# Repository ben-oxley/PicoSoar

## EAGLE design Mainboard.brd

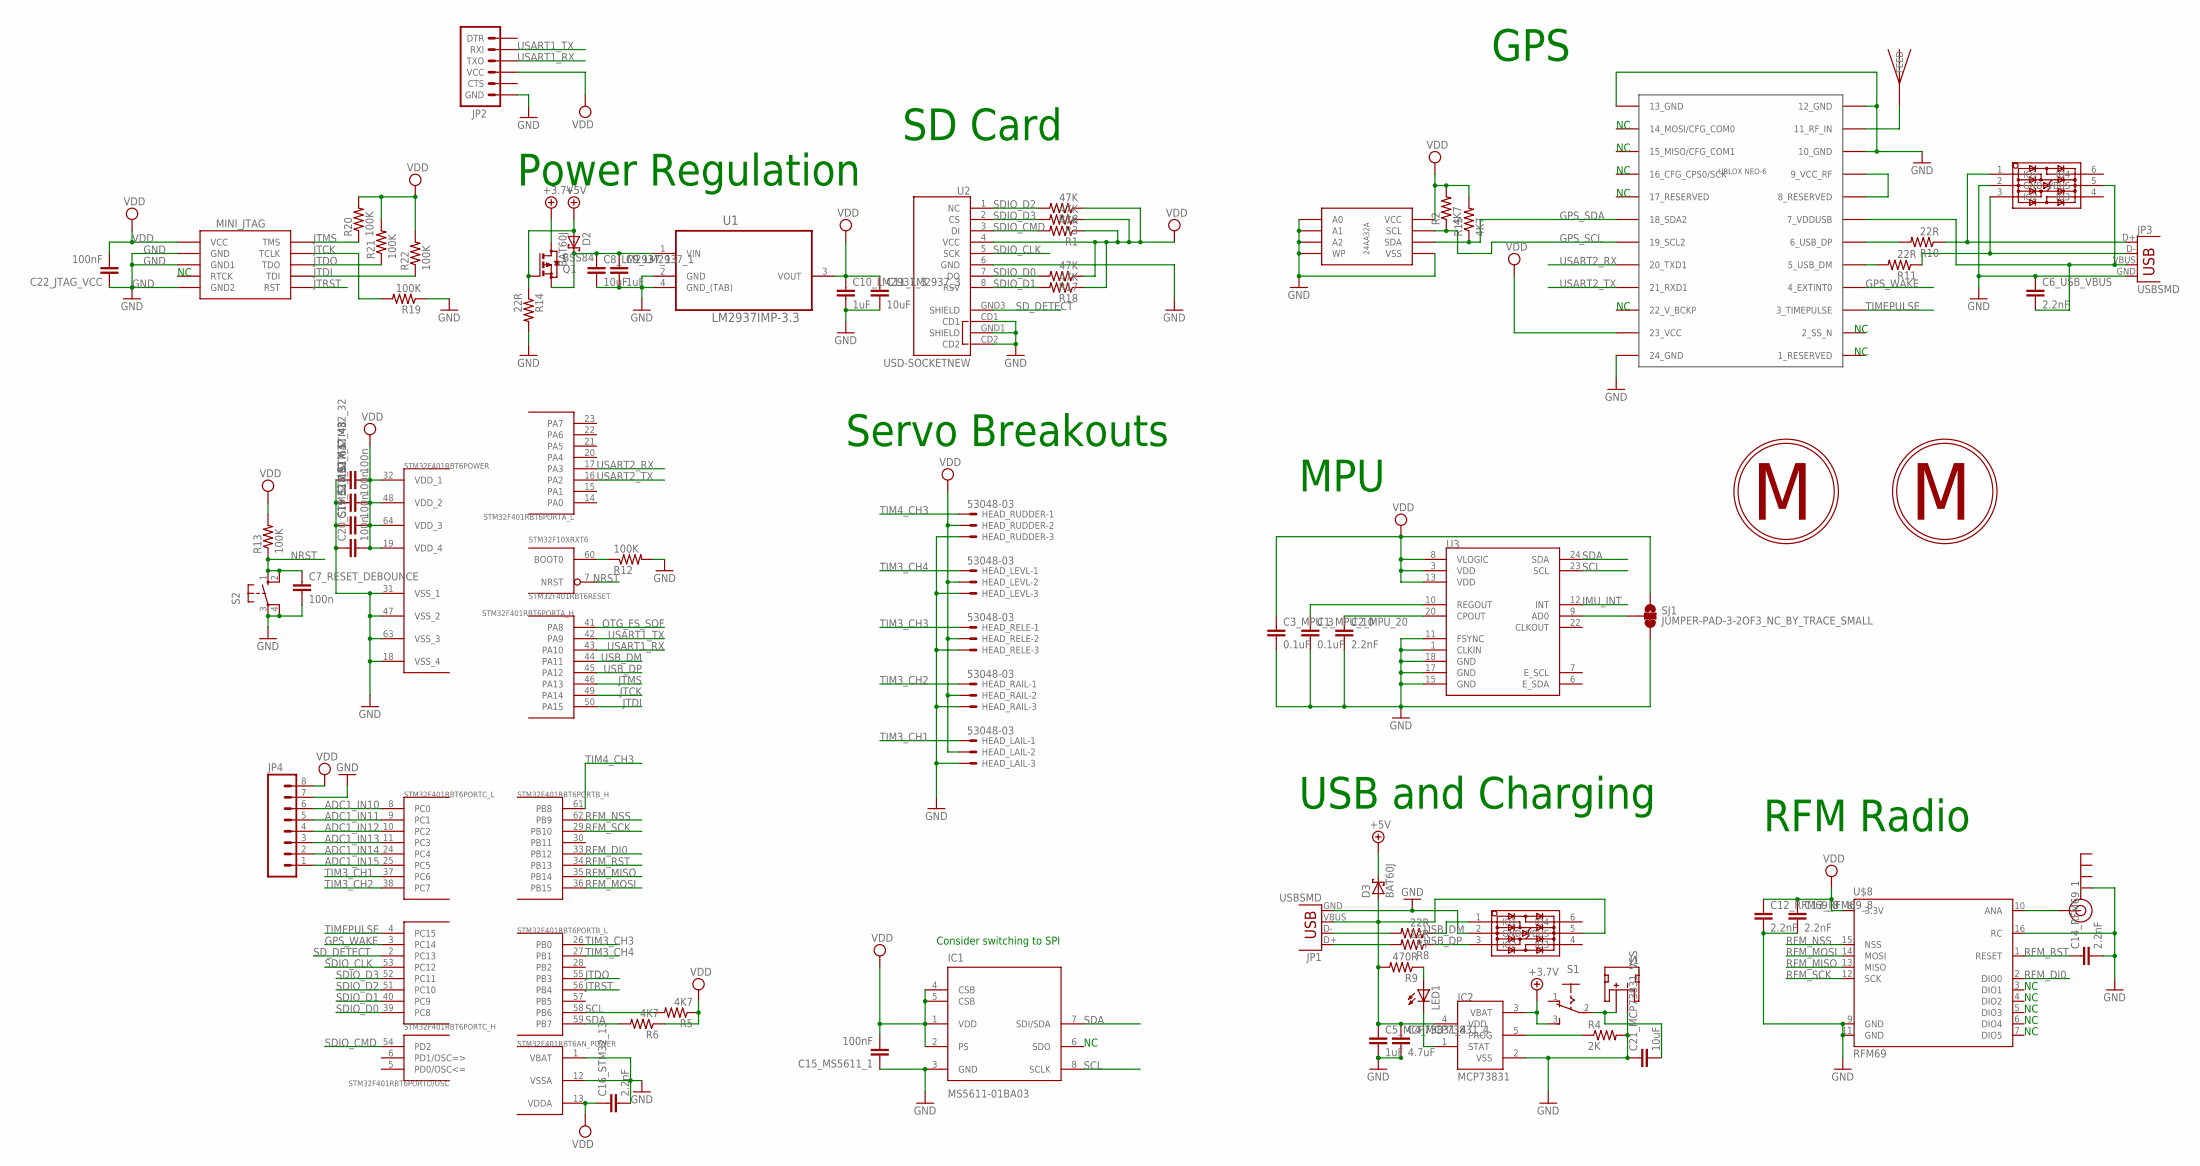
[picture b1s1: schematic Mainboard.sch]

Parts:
C1_MPU_10, C3_MPU_3: 0.1uF; 0805
C2_MPU_20, C6_USB_VBUS, C12_RFM69_8, C13_RFM69_8, C14_RFM69_1, C16_STM32_13: 2.2nF; 0805
C4_MCP73831_4: 4.7uF; 0805
C5_MCP73831_4, C9_LM2937_1, C10_LM2937_3: 1uF; 0805
C7_RESET_DEBOUNCE, C17_STM32_32, C18_STM32_48, C19_STM32_64, C20_STM32_19: 100n; 0805
C8_LM2937_1, C11_LM2937_3, C21_MCP73831_VSS: 10uF; 0805
C15_MS5611_1, C22_JTAG_VCC: 100nF; 0805
D2, D3: BAT60J; SOD323_ST
HEAD_LAIL: 53048-03
HEAD_LEVL: 53048-03
HEAD_RAIL: 53048-03
HEAD_RELE: 53048-03
HEAD_RUDDER: 53048-03
IC1: MS5611-01BA03; SON125P300X500X100-8N
IC2: MCP73831; SOT23-5L
J1: JST_2MM_MALE; JST-2-SMD
J$1: SMA_EDGE; SMA-EDGE
JP1, JP3: USBSMD; USB-MINIB
JP2: ARDUINO_SERIAL_PROGRAMSMD; 1X06-SMD
JP4: M08BM08B-SRSS-TB; BM08B-SRSS-TB
LED1: LEDCHIP-LED0805; CHIP-LED0805
Q1: BSS84; SOT23
R1, R3, R16, R17, R18: 47K; 0805
R2, R5, R6, R15: 4K7; 0805
R4: 2K; 0805
R7, R8, R10, R11, R14: 22R; 0805
R9: 470R; 0805
R12, R13, R19, R20, R21, R22: 100K; 0805
S1: 255SB
S2: 10-XX; B3F-10XX
SJ1: JUMPER-PAD-3-2OF3_NC_BY_TRACE_SMALL; PAD-JUMPER-3-2OF3_NC_BY_TRACE_YES_SILK_FULL_BOX
STM32F401RBT6: STM32F10XRXT6; TQFP64
U1: LM2937IMP-3.3; SOT230P700X180-4N
U2: USD-SOCKETNEW; MICRO-SD-SOCKET-PP
U3: MPU-9150QFN-24-NP; QFN-24-NP
U$1, U$6: USBLC6-4; SOT23-6
U$2: JTAG_MINI
U$3: I2C_EEPROM_24AA32A; MSOP8
U$4: JTI_ANTENNA-1575AT43A40
U$5: UBLOX_NEO-6; UBLOX_NEO-6P
U$7, U$9: SERVO; HK3D-1.7L
U$8: RFM69; RFM69SMD

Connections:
+4.1V: IC2.3 (VBAT), Q1.3 (D), S1.3 (S)
+5V: D2.A, D3.C, Q1.1 (G), R14.1
ADC1_IN10: JP4.6, STM32F401RBT6.8 (PC0)
ADC1_IN11: JP4.5, STM32F401RBT6.9 (PC1)
ADC1_IN12: JP4.4, STM32F401RBT6.10 (PC2)
ADC1_IN13: JP4.3, STM32F401RBT6.11 (PC3)
ADC1_IN14: JP4.2, STM32F401RBT6.24 (PC4)
ADC1_IN15: JP4.1, STM32F401RBT6.25 (PC5)
GND: C1_MPU_10.2, C2_MPU_20.2, C3_MPU_3.2, C4_MCP73831_4.2, C5_MCP73831_4.2, C6_USB_VBUS.1, C7_RESET_DEBOUNCE.2, C8_LM2937_1.2, C9_LM2937_1.2, C10_LM2937_3.2, C11_LM2937_3.2, C12_RFM69_8.2, C13_RFM69_8.2, C14_RFM69_1.2, C15_MS5611_1.1, C16_STM32_13.2, C17_STM32_32.1, C18_STM32_48.1, C19_STM32_64.1, C20_STM32_19.1, C21_MCP73831_VSS.1, C22_JTAG_VCC.1, HEAD_LAIL.3, HEAD_LEVL.3, HEAD_RAIL.3, HEAD_RELE.3, HEAD_RUDDER.3, IC1.3 (GND), IC2.2 (VSS), J1.1 (-), J$1.GND@0 (GND), JP1.GND, JP2.6 (GND), JP3.GND, JP4.7, R4.2, R12.2, R14.2, R19.1, S2.3, S2.4 (P1), SJ1.3, STM32F401RBT6.1 (VBAT), STM32F401RBT6.12 (VSSA), STM32F401RBT6.18 (VSS_4), STM32F401RBT6.31 (VSS_1), STM32F401RBT6.47 (VSS_2), STM32F401RBT6.63 (VSS_3), U1.2 (GND), U1.4 (GND_(TAB)), U2.6 (GND), U2.CD1, U2.CD2, U2.GND1 (SHIELD), U3.1 (CLKIN), U3.11 (FSYNC), U3.15 (GND), U3.17 (GND), U3.18 (GND), U$1.2 (GND), U$2.3 (GND), U$2.5 (GND1), U$2.9 (GND2), U$3.1 (A0), U$3.2 (A1), U$3.3 (A2), U$3.4 (VSS), U$3.7 (WP), U$5.10_GND, U$5.12_GND, U$5.13_GND, U$5.24_GND, U$6.2 (GND), U$8.9 (GND), U$8.11 (GND), U$8.16 (RC)
GPS_SCL: R2.1, U$3.6 (SCL), U$5.19_SCL2
GPS_SDA: R15.1, U$3.5 (SDA), U$5.18_SDA2
GPS_WAKE: STM32F401RBT6.3 (PC14), U$5.4_EXTINT0
IMU_INT: U3.12 (INT)
JTCK: R19.2, STM32F401RBT6.49 (PA14), U$2.4 (TCLK)
JTDI: R22.1, STM32F401RBT6.50 (PA15), U$2.8 (TDI)
JTDO: R21.1, STM32F401RBT6.55 (PB3), U$2.6 (TDO)
JTMS: R20.1, STM32F401RBT6.46 (PA13), U$2.2 (TMS)
JTRST: STM32F401RBT6.56 (PB4), U$2.10 (RST)
unnamed: C4_MCP73831_4.1, C5_MCP73831_4.1, D3.A, IC2.4 (VDD), JP1.VBUS, R9.2, U$6.5 (VBUS)
unnamed: C21_MCP73831_VSS.2, J1.2 (+), S1.2
unnamed: J$1.SIG (SIGNAL), U$8.10 (ANA)
unnamed: C8_LM2937_1.1, C9_LM2937_1.1, D2.C, Q1.2 (S), U1.1 (VIN)
unnamed: U$4.FEED, U$5.11_RF_IN
unnamed: SJ1.2, U3.9 (AD0)
unnamed: JP1.D+, R8.2
unnamed: JP1.D-, R7.2
unnamed: C1_MPU_10.1, U3.10 (REGOUT)
unnamed: IC2.5 (PROG), R4.1
unnamed: C2_MPU_20.1, U3.20 (CPOUT)
unnamed: LED1.A, R9.1
unnamed: IC2.1 (STAT), LED1.C
unnamed: JP3.D+, R10.1, U$1.1 (IO1)
unnamed: JP3.D-, R11.1, U$1.3 (IO2)
unnamed: R10.2, U$5.6_USB_DP
unnamed: R11.2, U$5.5_USB_DM
unnamed: C6_USB_VBUS.2, JP3.VBUS, U$1.5 (VBUS), U$5.7_VDDUSB
unnamed: U$5.8_RESERVED, U$5.9_VCC_RF
unnamed: R12.1, STM32F401RBT6.60 (BOOT0)
NRST: C7_RESET_DEBOUNCE.1, R13.1, S2.1 (S), S2.2 (S1), STM32F401RBT6.7 (NRST)
OTG_FS_SOF: STM32F401RBT6.41 (PA8)
RFM_DI0: STM32F401RBT6.33 (PB12), U$8.2 (DIO0)
RFM_MISO: STM32F401RBT6.35 (PB14), U$8.13 (MISO)
RFM_MOSI: STM32F401RBT6.36 (PB15), U$8.14 (MOSI)
RFM_NSS: STM32F401RBT6.62 (PB9), U$8.15 (NSS)
RFM_RST: C14_RFM69_1.1, STM32F401RBT6.34 (PB13), U$8.1 (RESET)
RFM_SCK: STM32F401RBT6.29 (PB10), U$8.12 (SCK)
SCL: IC1.8 (SCLK), R5.2, STM32F401RBT6.58 (PB6), U3.23 (SCL)
SDA: IC1.7 (SDI/SDA), R6.2, STM32F401RBT6.59 (PB7), U3.24 (SDA)
SDIO_CLK: STM32F401RBT6.53 (PC12), U2.5 (SCK)
SDIO_CMD: R1.2, STM32F401RBT6.54 (PD2), U2.3 (DI)
SDIO_D0: R17.2, STM32F401RBT6.39 (PC8), U2.7 (DO)
SDIO_D1: R18.2, STM32F401RBT6.40 (PC9), U2.8 (RSV)
SDIO_D2: R16.2, STM32F401RBT6.51 (PC10), U2.1 (NC)
SDIO_D3: R3.2, STM32F401RBT6.52 (PC11), U2.2 (CS)
SD_DETECT: STM32F401RBT6.2 (PC13), U2.GND3 (SHIELD)
TIM3_CH1: HEAD_LAIL.1, STM32F401RBT6.37 (PC6)
TIM3_CH2: HEAD_RAIL.1, STM32F401RBT6.38 (PC7)
TIM3_CH3: HEAD_RELE.1, STM32F401RBT6.26 (PB0)
TIM3_CH4: HEAD_LEVL.1, STM32F401RBT6.27 (PB1)
TIM4_CH3: HEAD_RUDDER.1, STM32F401RBT6.61 (PB8)
TIMEPULSE: STM32F401RBT6.4 (PC15), U$5.3_TIMEPULSE
USART1_RX: JP2.3 (TXO), STM32F401RBT6.43 (PA10)
USART1_TX: JP2.2 (RXI), STM32F401RBT6.42 (PA9)
USART2_RX: STM32F401RBT6.17 (PA3), U$5.20_TXD1
USART2_TX: STM32F401RBT6.16 (PA2), U$5.21_RXD1
USB_DM: R7.1, STM32F401RBT6.44 (PA11), U$6.1 (IO1)
USB_DP: R8.1, STM32F401RBT6.45 (PA12), U$6.3 (IO2)
VDD: C3_MPU_3.1, C10_LM2937_3.1, C11_LM2937_3.1, C12_RFM69_8.1, C13_RFM69_8.1, C15_MS5611_1.2, C16_STM32_13.1, C17_STM32_32.2, C18_STM32_48.2, C19_STM32_64.2, C20_STM32_19.2, C22_JTAG_VCC.2, HEAD_LAIL.2, HEAD_LEVL.2, HEAD_RAIL.2, HEAD_RELE.2, HEAD_RUDDER.2, IC1.1 (VDD), IC1.2 (PS), IC1.4 (CSB), IC1.5 (CSB), JP2.4 (VCC), JP4.8, R1.1, R2.2, R3.1, R5.1, R6.1, R13.2, R15.2, R16.1, R17.1, R18.1, R20.2, R21.2, R22.2, SJ1.1, STM32F401RBT6.13 (VDDA), STM32F401RBT6.19 (VDD_4), STM32F401RBT6.32 (VDD_1), STM32F401RBT6.48 (VDD_2), STM32F401RBT6.64 (VDD_3), U1.3 (VOUT), U2.4 (VCC), U3.3 (VDD), U3.8 (VLOGIC), U3.13 (VDD), U$2.1 (VCC), U$3.8 (VCC), U$5.23_VCC, U$8.8 (3.3V)

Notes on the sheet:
Consider switching to SPI
SD Card
Servo Breakouts
RFM Radio
USB and Charging
MPU
GPS
Power Regulation

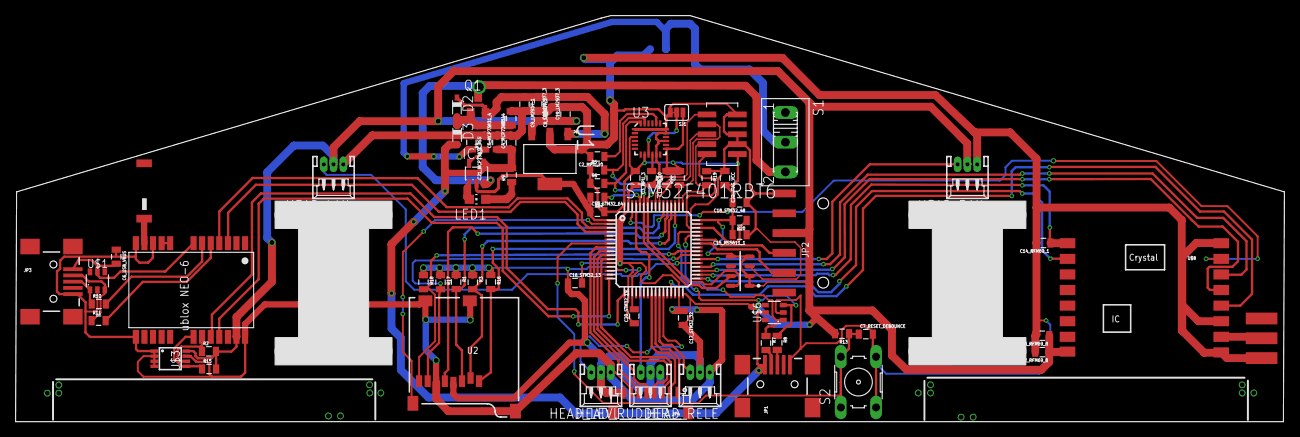
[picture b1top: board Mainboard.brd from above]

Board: 2 copper layers, 162.7 x 52.1 mm, 77 parts (1 on the bottom side), 66 nets.

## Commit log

2015-12-03 Added PDFs and initial schematic
2015-12-07 Fixed JTAG connector and rewired SDIO
2015-12-07 Tidied board layout
2015-12-07 Removed board
2015-12-07 Updated schematic
2015-12-08 Updated board design
2015-12-08 Updated board and schematic, added power switch. changed connectors. Improved wing shape.
2015-12-29 Updated PCB and added calculations spreadsheet
2015-12-29 Started initial routing
2015-12-29 Board rearranged
2015-12-31 Started wiring board
2015-12-31 Further routing
2015-12-31 Switched board layout wind cutouts
2016-03-18 Updated board wiring
2016-03-18 Routed all remaining air wires
2016-03-18 Fixed DRC errors
2016-03-18 Fixed ERC errors
2016-03-18 Fixed aileron slots
2016-03-19 Created 3D housing
2016-03-19 Rendered stl
2016-03-19 Updated design and stl
2016-03-19 Updated scad design
2016-03-19 Added aileron cutouts
2016-03-19 Updated case
2016-03-19 Increased thickness of case
2016-03-19 Tweaks to board design
2016-03-19 New case designs

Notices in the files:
parts and their libraries:
SparkFun-Capacitors: Licensing: Creative Commons ShareAlike 4.0 International - https://creativecommons.org/licenses/by-sa/4.0
